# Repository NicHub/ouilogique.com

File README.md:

# ouilogique.com

Fichiers du blog [ouilogique.com](https://ouilogique.com).

Pour visionner le site localement :

```bash
bash _serve.sh
```

❊

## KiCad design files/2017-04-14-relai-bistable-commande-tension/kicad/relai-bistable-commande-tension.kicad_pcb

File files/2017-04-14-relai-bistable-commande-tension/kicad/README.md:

# 2017-04-20

Envoyé les PCB pour fabrication à SeeedStudio.

<https://www.seeedstudio.com/fusion_pcb.html>

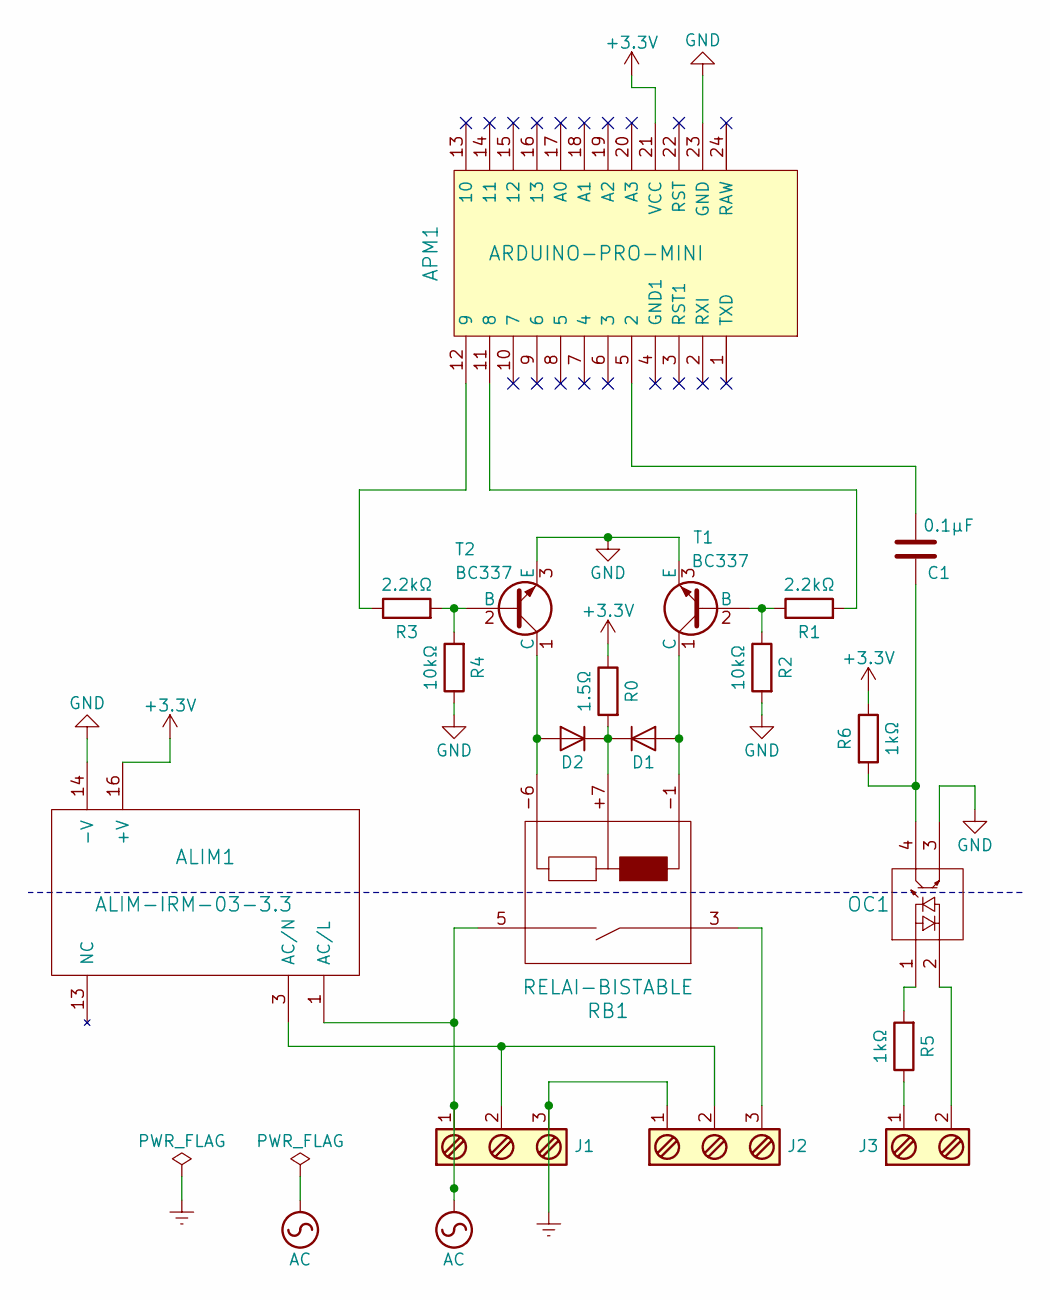
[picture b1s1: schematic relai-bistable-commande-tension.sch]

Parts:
ALIM1: ALIM-IRM-03-3.3; AC-DC_power_supply_IRM-03
APM1: ARDUINO-PRO-MINI; Arduino_Pro_Mini
C1: 0.1µF; CP_Radial_D5.0mm_P2.50mm
D1, D2: D_DO-41_SOD81_P7.62mm_Horizontal
J1, J2: PhoenixContact_MC-G_03x5.08mm_Angled
J3: PhoenixContact_MC-G_02x5.08mm_Angled
OC1: Optocoupleur_SFH620
R0: 1.5Ω; Resistor_Horizontal_RM7mm
R1, R3: 2.2kΩ; Resistor_Horizontal_RM7mm
R2, R4: 10kΩ; Resistor_Horizontal_RM7mm
R5, R6: 1kΩ; Resistor_Horizontal_RM7mm
RB1: RELAI-BISTABLE
T1, T2: BC337; TO-92_Inline_Narrow_Oval

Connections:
+3V3: ALIM1.16 (+V), APM1.21 (VCC), R0.1, R6.1
AC: ALIM1.1 (AC/L), J1.1, RB1.5
Earth: J1.3, J2.1
GND: ALIM1.14 (-V), APM1.23 (GND), OC1.3, R2.2, R4.1, T1.3 (E), T2.3 (E)
unnamed: ALIM1.3 (AC/N), J1.2, J2.2
unnamed: APM1.5 (2), C1.2
unnamed: APM1.11 (8), R1.2
unnamed: APM1.12 (9), R3.1
unnamed: C1.1, OC1.4, R6.2
unnamed: D1.1 (K), D2.1 (K), R0.2, RB1.+7
unnamed: D1.2 (A), RB1.-1, T1.1 (C)
unnamed: D2.2 (A), RB1.-6, T2.1 (C)
unnamed: J2.3, RB1.3
unnamed: J3.1, R5.1
unnamed: J3.2, OC1.2
unnamed: OC1.1, R5.2
unnamed: R1.1, R2.1, T1.2 (B)
unnamed: R3.2, R4.2, T2.2 (B)

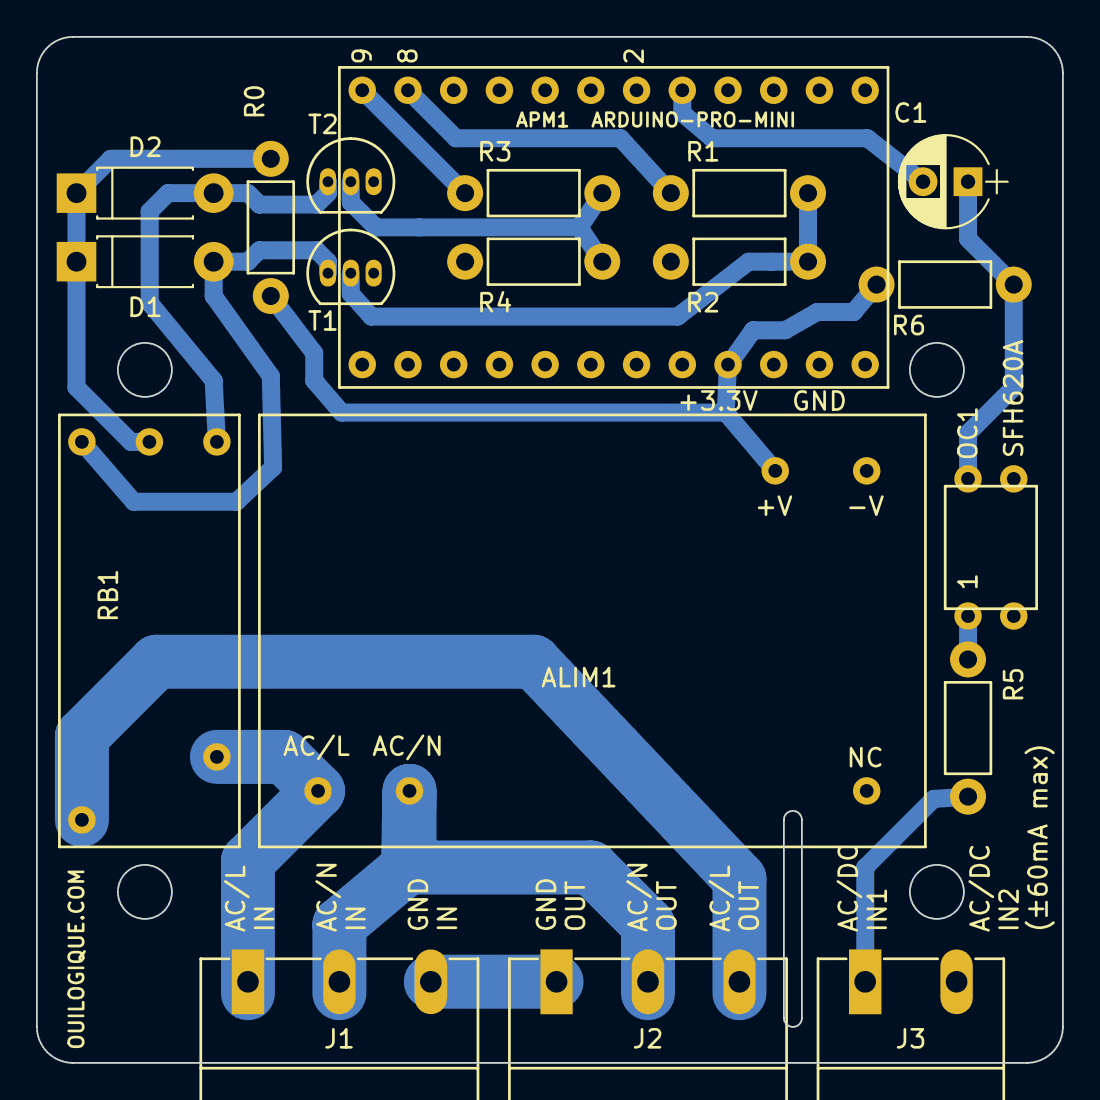
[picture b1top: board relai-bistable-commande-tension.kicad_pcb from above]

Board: 2 copper layers, 57.0 x 57.0 mm, 19 parts (0 on the bottom side), 18 nets.

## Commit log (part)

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2017-04-19 modif PCB Kicad
2017-04-19 images carousel pour pinout et relai bistable
2017-04-19 pcb kicad
2017-04-19 plan de masse PCB
2017-04-20 final
2017-04-20 kicad final
2017-04-20 PCB envoyé à SeeedStudio
2017-04-27 2017-04-27-neopixel-didel-ws2813
2017-04-28 update nRF24
2017-04-28 nRF24 ajout ESP8266
2017-04-29 ajout enum + scratchpad
2017-04-29 cleanup
2017-05-11 BMP280
2017-05-11 corrections
2017-05-11 image clicable
2017-05-16 bmp280 + TFT screen
2017-05-21 TFT screen + mosquitto MQTT + TS100 iron
2017-05-22 sandwich de WEMOS
2017-05-27 Arduino Pro Mini as ISP
2017-06-01 ajout images matrices avec tissu
2017-06-05 ajout gphoto2
2017-06-05 modif gphoto2
2017-06-07 ajout photos PCB relai bistable
2017-06-07 ajout image relai lit électrique installé
2017-06-09 relai bistable version PCB
2017-06-14 modif image top relai bistable
2017-06-19 esp8266-encodeur-rotatif-KY-040-websocket
2017-06-23 manipulation_des_ports ESP8266
2017-07-12 fausse modif
2017-07-15 2015-05-21-ch340_driver.md
2017-08-12 gphoto + mppt
2017-08-12 gems -> plugins dans _config.yml
2017-08-26 installation de Raspbian Stretch + installation de GPhoto2
2017-08-26 gphoto2
2017-08-26 Raspian Stretch
2017-09-18 MQTT
2017-09-30 piezo switch
2017-09-30 piezo-switch
2017-10-22 humour matplotlib
2017-11-12 ajouté quelques infos sur page Matplotlib
2017-11-12 modif humour-matplotlib
2018-01-24 Connecteur EIAJ
2018-01-24 ajout de cours HTML embarqué
2018-02-17 cours HTML embarqué
2018-02-17 navigation au clavier
2018-02-25 usb-rs232_bridge_microcontroleurs => ajout UART
2018-03-03 neopixel-didel-ws2813 + navigation clavier
2018-03-04 ajout RPi pour WS2813
2018-03-04 corrections WS2813
2018-04-22 2018-04-22-neopixel-raspberry-pi
2018-05-19 servo moteur
2018-06-30 Fausse modif pour transition HTTPS
2018-06-30 modif http -> https
2018-07-15 modif install raspbian stretch + ajout hack RF433
2018-07-15 hack RF433
2018-07-23 cleanup + correction lien Raspbian Stretch
2018-07-23 .gitignore
2018-07-26 correction id dans page.html
2018-07-29 lien pin à utiliser ESP
2018-10-14 Monter un disque sur rPi avec samba
2018-10-21 install python 3.6 + python aide-mémoire
2018-10-21 python 3.6 raspberry
2018-10-30 install Python 3.6 sur rPi
2019-01-01 ajout lien Google HTML/CSS Style Guide
2019-01-01 ajout lien Google HTML/CSS Style Guide + petites corrections
2019-01-24 ajout divers/rejoignez-la-resistance.jpg
2019-01-29 ajout PDF pour PCB + modif image DFPlayer
2019-01-29 ajout réf connecteur dans article relai bistable
2019-01-29 enlevés répertoire “articles”
2019-01-29 changement des niveaux des titres
2019-01-29 remplacé h1 par p dans header + style print
2019-01-29 update humour avec Matplotlib
2019-02-07 ajout M5STACK
2019-02-23 servomoteur + raspian stretch
2019-02-26 pinout esp32
2019-02-27 documentation inversion SPK1 et SPK2
2019-03-01 fausse modi
2019-03-21 modif pinout ESP32 + ajout image proto plateforme de Stewart
2019-03-21 renommé proto plateforme de Stewart
2019-03-21 enlevé bit exécution à proto plateforme de Stewart
2019-03-24 update pinouts
2019-03-27 plateforme-de-stewart-esp32
2019-03-27 stewart platform
2019-04-10 pins à ne pas utiliser sur ESP32
2019-04-25 aide-mémoire plateforme de Stewart
2019-04-25 cleanup plateforme de Stewart
2019-04-25 plateforme de Stewart -> liens + cleanup
2019-05-03 ajout image plateforme de Stewart
2019-05-03 ajout images plateforme de Stewart
2019-05-24 lien scratchapixel
2019-05-28 plateforme de Stewart
2019-05-31 Stewart platform v3
2019-06-22 ajout de vidéos plateforme de Stewart
2019-07-04 nouveaux lien plateforme de Stewart
2019-07-19 stewart
2019-07-26 Débuggage ESP32
2019-09-08 Article STM32-E407
2019-09-08 Gestion de "lang" et validation
2019-09-08 W3 validation
2019-09-08 renommé *.html => *.liquid
2019-10-12 ESP Prog
2019-10-19 Install RPi
2019-10-19 Livres
2019-11-04 Liens Martin
2020-02-02 DELTA-ROBOT ONE
2020-02-02 Lien PCA9685 Mouser
2020-02-22 arduino mega pinout
2020-02-22 update _serve
2020-02-29 esp32-pinout-reference-gpios
2020-03-14 analyseur logique Arduino
2020-05-25 humour magic word
2020-12-07 pinouts
2020-12-23 removed exec bit
2020-12-23 installer-raspian-stretch.md
2020-12-25 Installer Pi-hole sur un Raspberry
2020-12-26 Intro Pi-hole
2020-12-26 Calques
2021-01-03 Ajout récup URL
2021-01-09 typo + liens
2021-02-28 Pi-hole
2021-04-17 fausse modif test PAT
2021-04-24 Plateforme de Stewart avec PCA9685
2021-06-12 Dependabot vulnerable dependencies remediation
2021-08-30 magic-word.jpg
2021-11-28 tmux update
2021-11-28 Update Raspian Stretch
2021-12-02 MANTRA
2021-12-02 Suppression du menu « recherche »
2021-12-04 External interrupts on the ATmega168/328
2021-12-12 VNC RPi
2021-12-26 stewart + esp-prog
2021-12-26 esp-prog update
2022-01-03 picocom
2022-01-07 Update page intro
2022-01-07 Corrigé HTML de l’index
2022-04-05 update stewart platform links
2022-04-05 images
2022-04-05 optim images
2022-04-05 enlevé img
2022-04-05 change stewart banner
2022-06-19 Stewy
2022-06-19 There is no place like 127.0.0.1
2022-06-19 rename there-is-no-place-like-127_0_0_1.jpg
2022-06-21 links
2022-08-10 tables ASCII
2022-08-14 Ajout capture écran table ASCII
2022-08-14 Plug and Eject disk rPi
2022-11-27 fichiers P19
2023-01-15 update stretch
2023-01-29 correction des liens
2023-01-30 Détails plateforme de Stewart
2023-02-03 ajout de analytics g4
2023-02-03 Fix analyticstracking-g4.liquid name
2023-02-18 corrected bad links
2023-02-18 Source+Sans+Pro from Google Fonts
2023-02-18 Add Volkhov font
2023-02-18 Mega cleanup
2023-03-04 update installer raspian stretch
2023-03-09 nouvelle page pour RPi
2023-03-09 Installer Raspberry Pi OS sur Raspberry Pi
2023-03-11 radios
2023-03-12 redirect radios vers ouilogique.ch
2023-03-24 photos composants
2023-04-02 update install rpi
2023-04-03 iframe radios
2023-04-03 no iframe radios
2023-04-20 Google font debug
2023-04-20 update playlist
2023-04-20 tout les flux en https
2023-04-20 Fromat playlist as json
2023-04-20 Upgrade jquery
2023-04-20 Analytics
2023-04-20 Link checkup
2023-05-16 rel icon
2023-05-16 png icon
2023-05-16 https streams
2023-05-16 ajout radios dans menu
2023-05-20 new favicon
2023-05-30 Flasher un bootloader
2023-05-30 Typos
2023-05-31 Update Flasher un bootloader
2023-06-15 Pinout S2
2023-07-04 Radio fonts
2023-07-04 favicon 16x16 pour Safari
2023-07-12 update stewy
2023-07-24 Enlevé Radio 74
2023-10-02 Adapt to Quarto
2023-10-02 Harmonisation des headers YAML
2023-10-14 Mise en forme cours HTML CSS JS
2023-10-14 ajout de nofollow aux liens cassés
2023-10-14 remis les liens internes en absolu pour l’instant
2023-10-14 Casse des titres
2023-10-15 modif structure répertoires pour corriger liens relatifs et éviter err 400
2023-10-15 petites corrections
2023-10-15 avoid err 400
2023-10-15 check links
2023-10-15 link check
2023-10-15 Changed LICENSE
2023-11-11 Condo ESP BOOT
2023-11-11 rename files
2023-12-23 Logo animé
2023-12-30 utf8 article
2023-12-31 N.B.
2024-01-20 split article chaine python
2024-01-25 false
2024-02-08 Nombre polygonal centré
2024-02-08 CPN bien finalisé
2024-02-09 Créé dépot séparé pour centered_polygonal_number_generator
2024-02-09 undelete favicon.svg
2024-03-10 cpn + icon
2024-04-14 Vidéo There is no place like 127.0.0.1
2024-04-14 stewy : Ajout condensateur 10 uF + modif images en conséquence
2024-04-20 AT commands
2024-04-21 stew IO35 to IO32
2024-04-27 typo
2024-04-30 How Flight Simulators Trick Your Brain
2024-06-26 enlevé analyticstracking
2024-08-12 caractéristiques intéressantes du code ASCII
2024-09-29 nofollow broken links
2025-01-02 Mention de Jakob
2025-01-02 alphabet grec
2025-02-19 taille utf8
2025-02-19 Bad links => {:rel="nofollow"}
2025-02-25 whatismyip
2025-03-03 removed ip
2025-03-03 update sites web statiques
2025-04-18 Pinout TTGO
2025-08-03 update ssh ed25519 dans rpi
2025-09-01 qrcode dans _serve
2025-09-21 link
2025-09-27 Supprimé CNAME
2025-09-27 cname
2025-11-17 Pinout Heltec
2026-02-08 chmod _serve
2026-02-09 Enlevé CNAME
2026-02-09 rename code-workspace
2026-02-09 Added robots.txt
